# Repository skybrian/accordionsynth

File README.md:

# An accordion synthesizer project

My goal is to eventually replicate the keyboard and sound of the bass side of an accordion in an electronic device that accordion players will find easy to adapt to. So far I've built three prototypes:

  * Prototype 1 was trying out a Teensy 4 with an audio shield on a breadboard, with 4 bass buttons.
  * For prototype 2, I put the buttons on two double-decker circuit boards (9 bass buttons).
   Here's the [Video](https://www.youtube.com/watch?v=f6V9Kw87OYE). You can see the remains of prototype 1 in the background.
  * For prototype 3, I built a real case out of wood and laser-cut acrylic panels, to make a desktop device that's more easily portable. This one uses a Teensy 3.6. Here's the [Video](https://www.youtube.com/watch?v=nj9DO6gRxgs). I designed it in Onshape and you can [look at the CAD model online](https://cad.onshape.com/documents/49e3bde7fd0cf848110a849c/w/f0f076d4e6eda68337d8a8fa/e/61a0bfc531c55ddd0f7d8f48).

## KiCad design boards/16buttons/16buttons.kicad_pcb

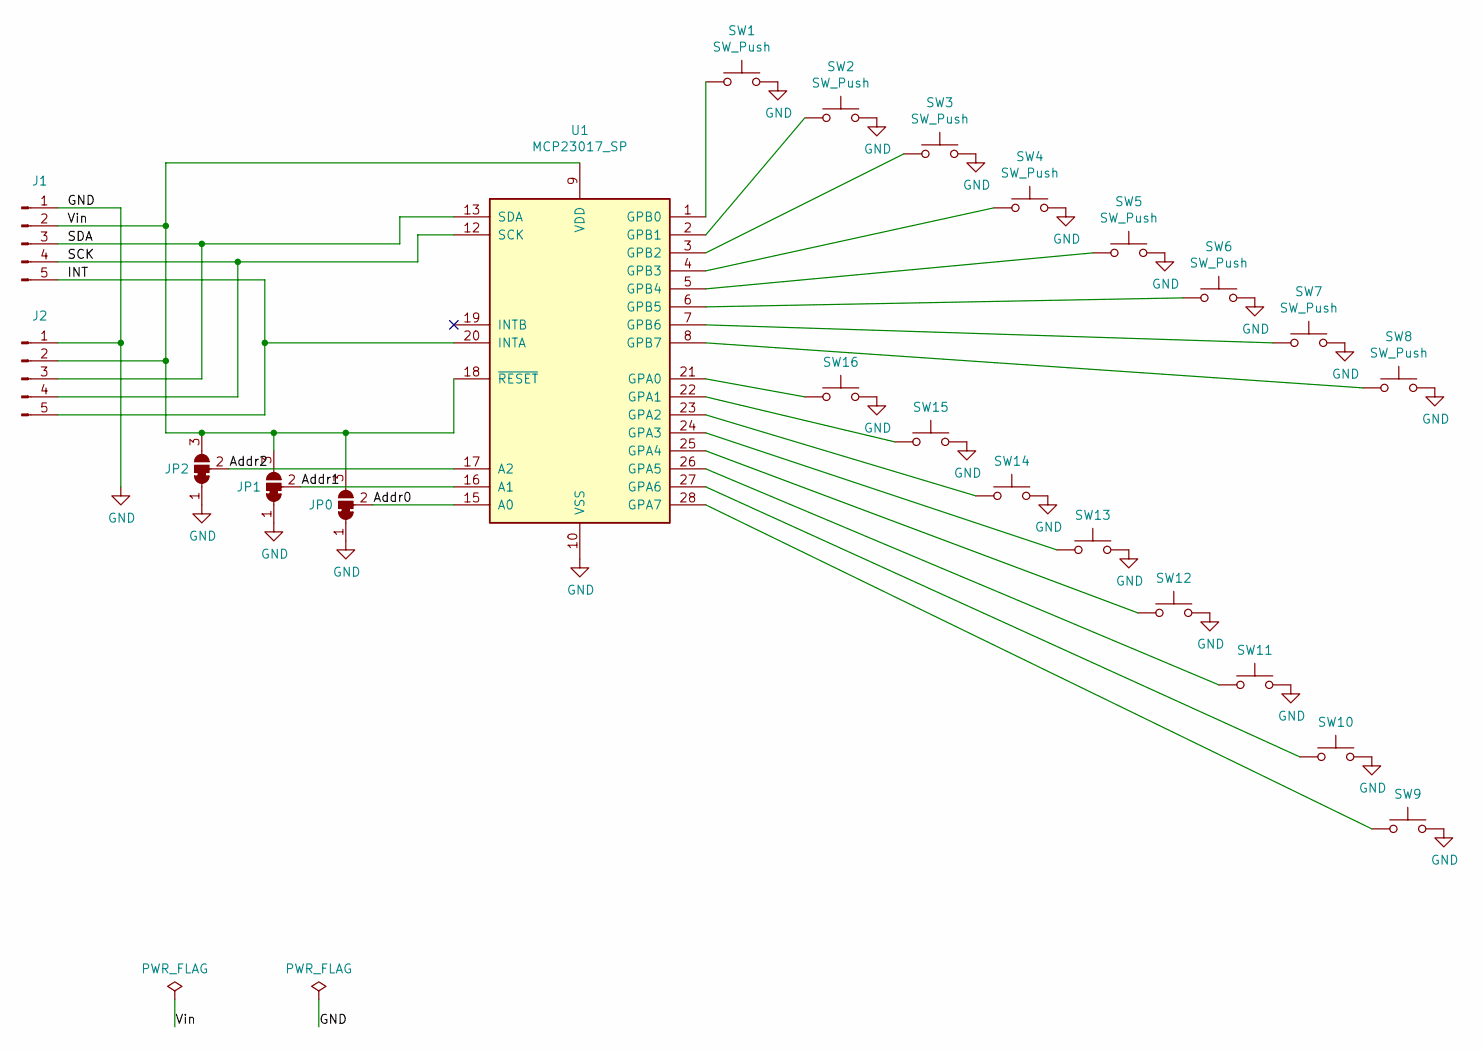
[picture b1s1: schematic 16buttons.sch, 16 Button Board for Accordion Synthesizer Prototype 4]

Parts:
J1, J2: i2c connector; PinHeader_i2c
JP0, JP1, JP2: SolderJumper; SolderJumper_Bridged12
SW1, SW2, SW3, SW4, SW5, SW6, SW7, SW8, SW9, SW10, SW11, SW12, SW13, SW14, SW15, SW16: SW_Push; SW_Gateron_Trim
U1: MCP23017_SP; DIP-28_W7.62mm

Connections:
/Addr0: JP0.2 (C), U1.15 (A0)
/Addr1: JP1.2 (C), U1.16 (A1)
/Addr2: JP2.2 (C), U1.17 (A2)
/INT: J1.5, J2.5, U1.20 (INTA)
/SCK: J1.4, J2.4, U1.12 (SCK)
/SDA: J1.3, J2.3, U1.13 (SDA)
/Vin: J1.2, J2.2, JP0.3 (B), JP1.3 (B), JP2.3 (B), U1.9 (VDD), U1.18 (~RESET~)
GND: J1.1, J2.1, JP0.1 (A), JP1.1 (A), JP2.1 (A), SW1.2, SW2.2, SW3.2, SW4.2, SW5.2, SW6.2, SW7.2, SW8.2, SW9.2, SW10.2, SW11.2, SW12.2, SW13.2, SW14.2, SW15.2, SW16.2, U1.10 (VSS)
unnamed: SW1.1, U1.1 (GPB0)
unnamed: SW2.1, U1.2 (GPB1)
unnamed: SW3.1, U1.3 (GPB2)
unnamed: SW4.1, U1.4 (GPB3)
unnamed: SW5.1, U1.5 (GPB4)
unnamed: SW6.1, U1.6 (GPB5)
unnamed: SW7.1, U1.7 (GPB6)
unnamed: SW8.1, U1.8 (GPB7)
unnamed: SW9.1, U1.28 (GPA7)
unnamed: SW10.1, U1.27 (GPA6)
unnamed: SW11.1, U1.26 (GPA5)
unnamed: SW12.1, U1.25 (GPA4)
unnamed: SW13.1, U1.24 (GPA3)
unnamed: SW14.1, U1.23 (GPA2)
unnamed: SW15.1, U1.22 (GPA1)
unnamed: SW16.1, U1.21 (GPA0)

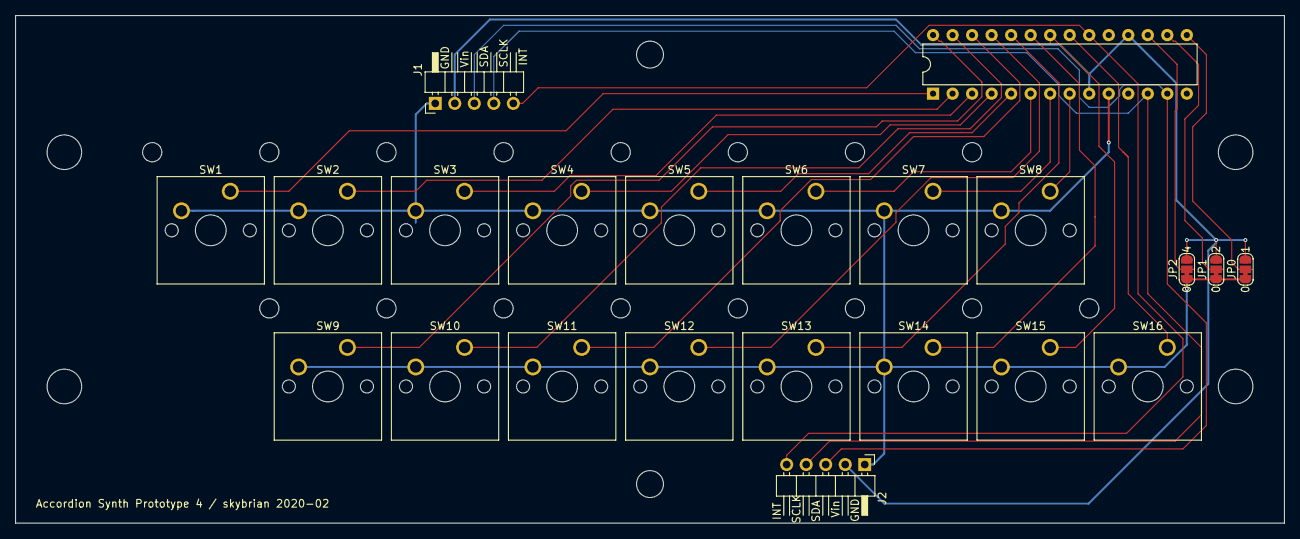
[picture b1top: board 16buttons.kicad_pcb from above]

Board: 2 copper layers, 165.1 x 66.0 mm, 22 parts (0 on the bottom side), 24 nets.

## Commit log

2019-11-04 Plays some notes
2019-11-05 introduce Reed
2019-11-05 introduce Bank
2019-11-06 add harmonics
2019-11-07 play to two different banks
2019-11-07 tweak audio
2019-11-07 4 bass buttons
2019-11-22 Now it's a 9-bass.
2019-11-24 add startup song, fix ghost keys
2019-12-17 Protoype 3 mostly working
2019-12-19 turn up volume, blink LED on startup
2019-12-31 enable MIDI controller (sends octaves though)
2019-12-31 use a different hack to handle multiple boards
2019-12-31 send the same notes to MIDI that will be played
2019-12-31 deep bass
2020-01-13 use Shepard tones for bottom bases
2020-01-13 switch to sawtooth and filter; E flat wasn't playing in C minor chord
2020-01-13 use two detuned sawtooth waves
2020-01-14 make detuned sawtooths actually work and fix bug where notes stopped working
2020-01-14 fix oscillator hard-sync, adjust envelope and Shepard tones
2020-01-15 tweak the sound a bit more
2020-01-20 add README pointing to video and CAD design
2020-01-31 add KiCAD project for proto 4 board
2020-02-01 board tweaks before OSH Park order
2020-02-01 add drawings for 16 button board
2020-02-06 improve sound when holding a button down
2020-02-15 now using hinge and accelerometer for bellows
2020-02-24 switch to using a gyro sensor for angular velocity
2020-02-24 refactor bellows code
2020-02-24 tweaked pressure curve
2020-02-25 switch to table for pressure curve
2020-05-02 try changing volume using left-right rocker
